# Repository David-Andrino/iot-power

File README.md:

# IoT - POWER

**David Andrino** 

**Estela Mora** 

**Fernando Sanz** 

**Hugo Sanchez**

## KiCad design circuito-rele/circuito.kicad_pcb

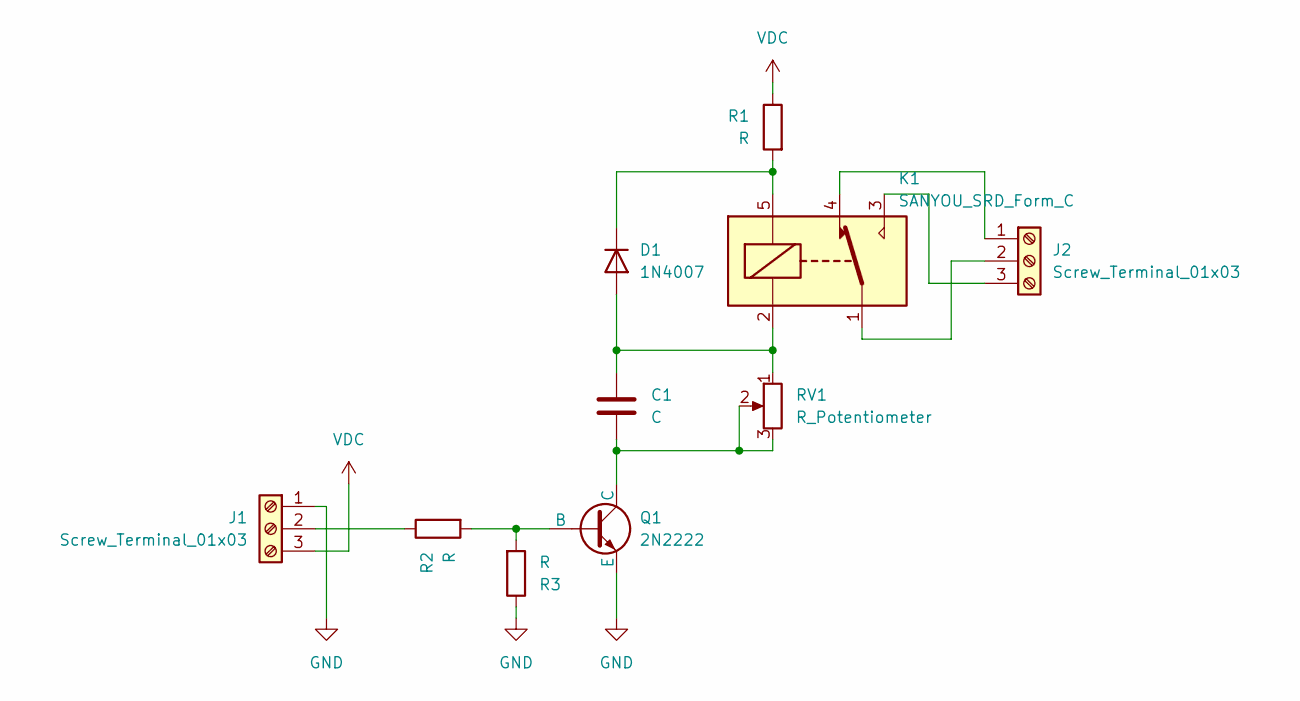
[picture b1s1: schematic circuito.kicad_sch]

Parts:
C1: C; CP_Radial_D12.5mm_P5.00mm
D1: 1N4007; D_DO-41_SOD81_P10.16mm_Horizontal
J1, J2: Screw_Terminal_01x03; TerminalBlock_bornier-3_P5.08mm
K1: SANYOU_SRD_Form_C; Relay_SPDT_SANYOU_SRD_Series_Form_C
Q1: 2N2222; TO-92L_HandSolder
R1, R2, R3: R; R_Axial_DIN0207_L6.3mm_D2.5mm_P10.16mm_Horizontal
RV1: R_Potentiometer; Potentiometer_ACP_CA9-V10_Vertical_Hole

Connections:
GND: J1.1, Q1.3 (E), R3.1
unnamed: C1.1, D1.2 (A), K1.2, RV1.1
unnamed: D1.1 (K), K1.5, R1.2
unnamed: J1.2, R2.1
unnamed: J2.1, K1.4
unnamed: J2.2, K1.1
unnamed: J2.3, K1.3
unnamed: Q1.2 (B), R2.2, R3.2
unnamed: C1.2, Q1.1 (C), RV1.2, RV1.3
VDC: J1.3, R1.1

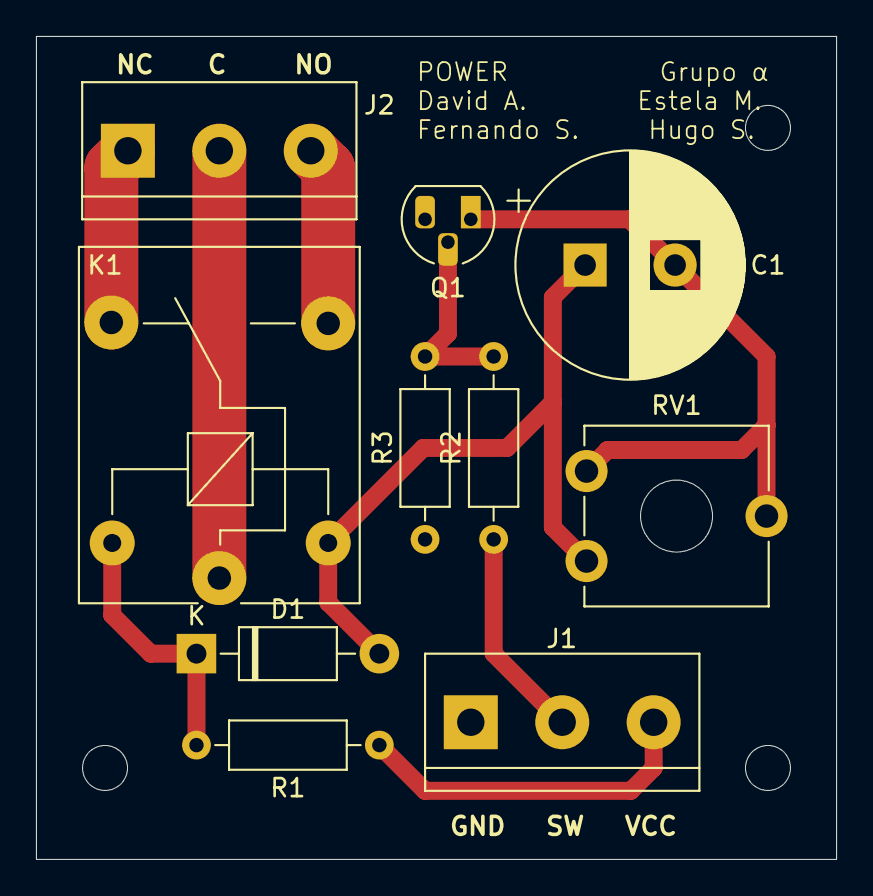
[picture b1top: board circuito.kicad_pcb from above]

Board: 2 copper layers, 44.5 x 45.7 mm, 10 parts (0 on the bottom side), 10 nets.

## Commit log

2024-11-08 Creación plantilla
2024-11-08 Actualización portada
2024-11-08 Limpieza de archivos
2024-11-08 Actualizar el main
2024-11-08 Primera compilación
2024-11-08 README.md
2024-11-08 Cabecero arreglado (URL)
2024-11-08 Ignore out
2024-11-08 Main
    Pendiente de modificarlo para añadir las cosas de fer
2024-11-11 Crear diagrama de circuito
2024-11-11 Remove backups
2024-11-19 Crear diagrama
2024-11-19 Terminar circuito
2024-11-19 Cambiar nombre de carpeta de circuito de rele
2024-11-19 Borrar README.md
    hugo bobo
2024-11-22 Grueso del código
    Fichero con el código terminado, quedan pendientes pruebas y hacer las medidas con cada dirección SPI.
2024-11-22 Envios Correctos
    Cambios para el envío al MQTT al topic correcto.
2024-11-22 Comprimir libreria
2024-11-22 Metodo de publicacion de medidas arreglado
2024-11-22 Eliminar publish
2024-11-27 Medidas_INA_Funcionando
    Pendiente Cambiar Direcciones INA para que corresponda con cada uno de los módulos
2024-11-29 Modularizar y comentar el codigo
2024-11-29 Modularizar mqtt client
2024-11-29 Testear modo sleep
2024-11-30 Medidas_Bajo_Consumo
    Medidas a petición (cambiar el loop por un metodo cunado lo juntemos todo) y tras las medidas bajo consumo
2024-12-04 Bajo Consumo + Modularizado + Documentado+ Test
    -Documentación:
    Fuente de la librería Arduino: https://github.com/wollewald/INA226_WE?tab=readme-ov-file
    Ejemplos de código:https://wolles-elektronikkiste.de/en/ina226-current-and-power-sensor
2024-12-04 Modulo completo del sistema.
2024-12-04 Crear workflow de Doxygen
2024-12-04 deploy: 7b1489c3625700c75bcdc055472a7e7efdf8022a
2024-12-04 deploy: 00c84a3bd9f2e3ef76efc43de4beac68f87a6c5c
2024-12-04 Update logo
2024-12-04 deploy: 419a05c96189d6aa0375860d783288f32d970159
2024-12-04 deploy: 82833343a09910bc009a1ee39ca7d641560627a2
2024-12-04 deploy: df610af531d218e87ae7e803fc4625fd438b42e1
2024-12-04 Añadir logo full
2024-12-04 deploy: 4ef246e284a6a411eee0c20315ad66d5830771ff
2024-12-04 Arreglar imagen en Doxygen
2024-12-04 deploy: e928c6dcf55c78d3e8daabfe31593d105361886d
2024-12-05 Ficheros en suelto
2024-12-05 Arreglar chapuza 1
2024-12-05 deploy: e676c20e964a1b826e1f2c6e566e32203fe64795
2024-12-05 Add file header to mqtt_client.hpp
2024-12-05 deploy: dc6d1465e7d51fed8cb98dc82904e4437c59b6fb
2024-12-08 Organizar la memoria
2024-12-09 Antibloqueante_Wifi_MQTT
2024-12-09 Ficheros Caja
2024-12-09 Escribir 2.1-DiagramaDeBloques
2024-12-11 Add write and read file
2024-12-12 Add RTC, write file and sleep in Main Power
2024-12-12 Corrección error conexion MQTT
2024-12-12 Añadidas las direcciones de los INA
2024-12-13 Crear estructura de submodulos hardware en la memoria
2024-12-13 Repartir modulos
2024-12-13 Codigo funcionando
2024-12-14 Add ThingsBoard memory part
2024-12-14 Adding mqtt broker and thingsboard installation steps
2024-12-15 Borrar codigo redundante
2024-12-15 Cambiar nombre de .h a .hpp y separar telemetry.hpp
2024-12-15 Cambiar new_sleep_mode a sleep
2024-12-15 Cambiar nombres de ina y file_management. Unificar write y read en uno
2024-12-15 Ponerle nombre a los pines de los reles
2024-12-15 Añadir TODO en sleep.hpp
2024-12-15 Reordenar funciones en file_management.cpp
2024-12-15 Ponerle nombres a los pines en MAIN_POWER.ino
2024-12-15 Eliminar comentarios y simplificar MAIN_POWER
2024-12-15 Actualizar comentarios en file_management
2024-12-15 Refactorizar modulo mqtt_client y cambiar comentarios
2024-12-15 Eliminar read_file.cpp
2024-12-15 Refactorizar sleep.cpp
2024-12-15 Refactorizar el main
2024-12-15 Añadir comentarios para el Doxygen
2024-12-15 deploy: 260165f54d6c6b6ef71c8f543888fc2a5cc6fc96
2024-12-15 Add Doxygen headers to all files
2024-12-15 deploy: 09bc176a9e3c062bf20b869e7ec26755a5bb98ae
2024-12-15 Arreglar comentario de telemetry.hpp
2024-12-15 deploy: 1dabc58623fc97c09b7614dba890c31239268953
2024-12-17 Crear bibliografía
2024-12-17 Módulo del LDO
2024-12-17 Modulo de descarga
2024-12-17 Módulo cargador de baterías
2024-12-18 Change format of url
2024-12-18 File manager and add telemetry.hpp
2024-12-18 deploy: cf0b33550b4a0bfb16395f506782325f4e68c74b
2024-12-18 P.O.W.E.R
2024-12-21 Cambiar estructura de la memoria
2024-12-21 Eliminar basura
2024-12-21 Añadir programa principal y lectura
2024-12-22 Create 3-2-1-ina
2024-12-22 Create a
2024-12-22 Create hoa
2024-12-22 IMAGENES INA
2024-12-22 IMAGENES MQTT
2024-12-22 IMAGENES CAJA
2024-12-22 LATEX INA SIN FOTOS
2024-12-22 LATEX MQTT SIN FOTOS
2024-12-22 LATEX MAIN INCOMPLETO
2024-12-22 LATEX CAJA SIN FOTOS
2024-12-23 Parte de memoria del panel solar
2024-12-23 Terminar parte panel solar memoria
2024-12-23 Parte del bajo consumo memoria
2024-12-23 Parte file_management memoria
2024-12-23 Introducción
2024-12-23 Módulo elevador
2024-12-23 Módulo reductor
2024-12-23 LDO images
2024-12-23 Baterías
2024-12-23 Programa de lectura memoria
2024-12-23 ESP8266
2024-12-23 INA226
2024-12-23 Bibliografía ESP8266, INA226, elevador y reductor
2024-12-23 Start reles.tex
2024-12-23 Change h to H on all figures
2024-12-23 Diagrama de bloques general actualizado
2024-12-23 Índice Montaje completo
2024-12-23 Circuito reles
2024-12-23 Conexionado
2024-12-23 Diagrama general.drawio
2024-12-24 Caracterizacion de componentes
2024-12-24 Arreglos Latex Caja
2024-12-24 Fichero Hardware en latex
2024-12-24 Telemetria latex
2024-12-24 INA CON IMAGENES
2024-12-25 Parte programa principal memoria
2024-12-25 Detalles elevador
2024-12-25 Foto del PCB de los reles
2024-12-25 Añadir diagrama de flujo programa pincipal
2024-12-25 MAIN CAMBIADO HUGO
2024-12-25 CAMBIOS PARA CODIGO
2024-12-26 Diagrama de estados
2024-12-26 Estados del sistema
2024-12-26 Conexionado general
2024-12-26 Añadir esquematico del circuito
2024-12-26 .gitignore .vscode
2024-12-26 Montaje/esquematico.tex
2024-12-26 Fix merge errors
2024-12-26 Presupuesto
2024-12-26 Explaination of battery protection
2024-12-26 Simple Block diagram
2024-12-26 Conexionado del sistema redactado
2024-12-26 Referencias
2024-12-28 Montaje completo
2024-12-28 Doxygen
2024-12-28 Remove memoria/images/ganttEstimado.png
2024-12-28 Tabla de las horas
2024-12-28 Write introduction to the Presupuesto table
2024-12-28 Fix typos
2024-12-28 Librerias
2024-12-28 Anexo fotos caja
2024-12-29 Fix TODOs and missing texttt
2024-12-29 Remove test requirement
2024-12-29 Elevadisima precision de los INA
2024-12-29 Encarecida recomendacion de pcb analogica
2024-12-29 Valor del potenciómetro
2024-12-29 inicialmente se comporta inicialmente
2024-12-29 Rewrite specification
2024-12-29 Add texttt and tabs to 3.1.1 and 3.2.1
2024-12-29 Cambiar PIN por GPIO en 3.2.2
2024-12-29 Textt and tabs on 3.2.3
2024-12-29 Hacer los todo de mis partes
2024-12-29 Typo on 3.2.4
2024-12-29 Add code to mqtt
2024-12-29 texttt en 3.2.5
2024-12-29 textt en shunt
2024-12-29 Typo on 3.2.5
2024-12-29 Errores gramaticales y monoespaciado
2024-12-29 Fix style
2024-12-29 Gramatical errors
2024-12-29 Change table names
2024-12-29 Memoria v1.1
2024-12-30 Remove panelSolar
2024-12-30 Memoria v1.2
2024-12-30 deploy: 9499f0dc0f13e067b07283105840138583d94db5
2024-12-30 Memoria 1.3 Anexo de código
2025-01-02 Ignore LaTeX on Doxygen
2025-01-02 deploy: 612bc0d194ab9b7ce0067c936ca3180cd091094c
